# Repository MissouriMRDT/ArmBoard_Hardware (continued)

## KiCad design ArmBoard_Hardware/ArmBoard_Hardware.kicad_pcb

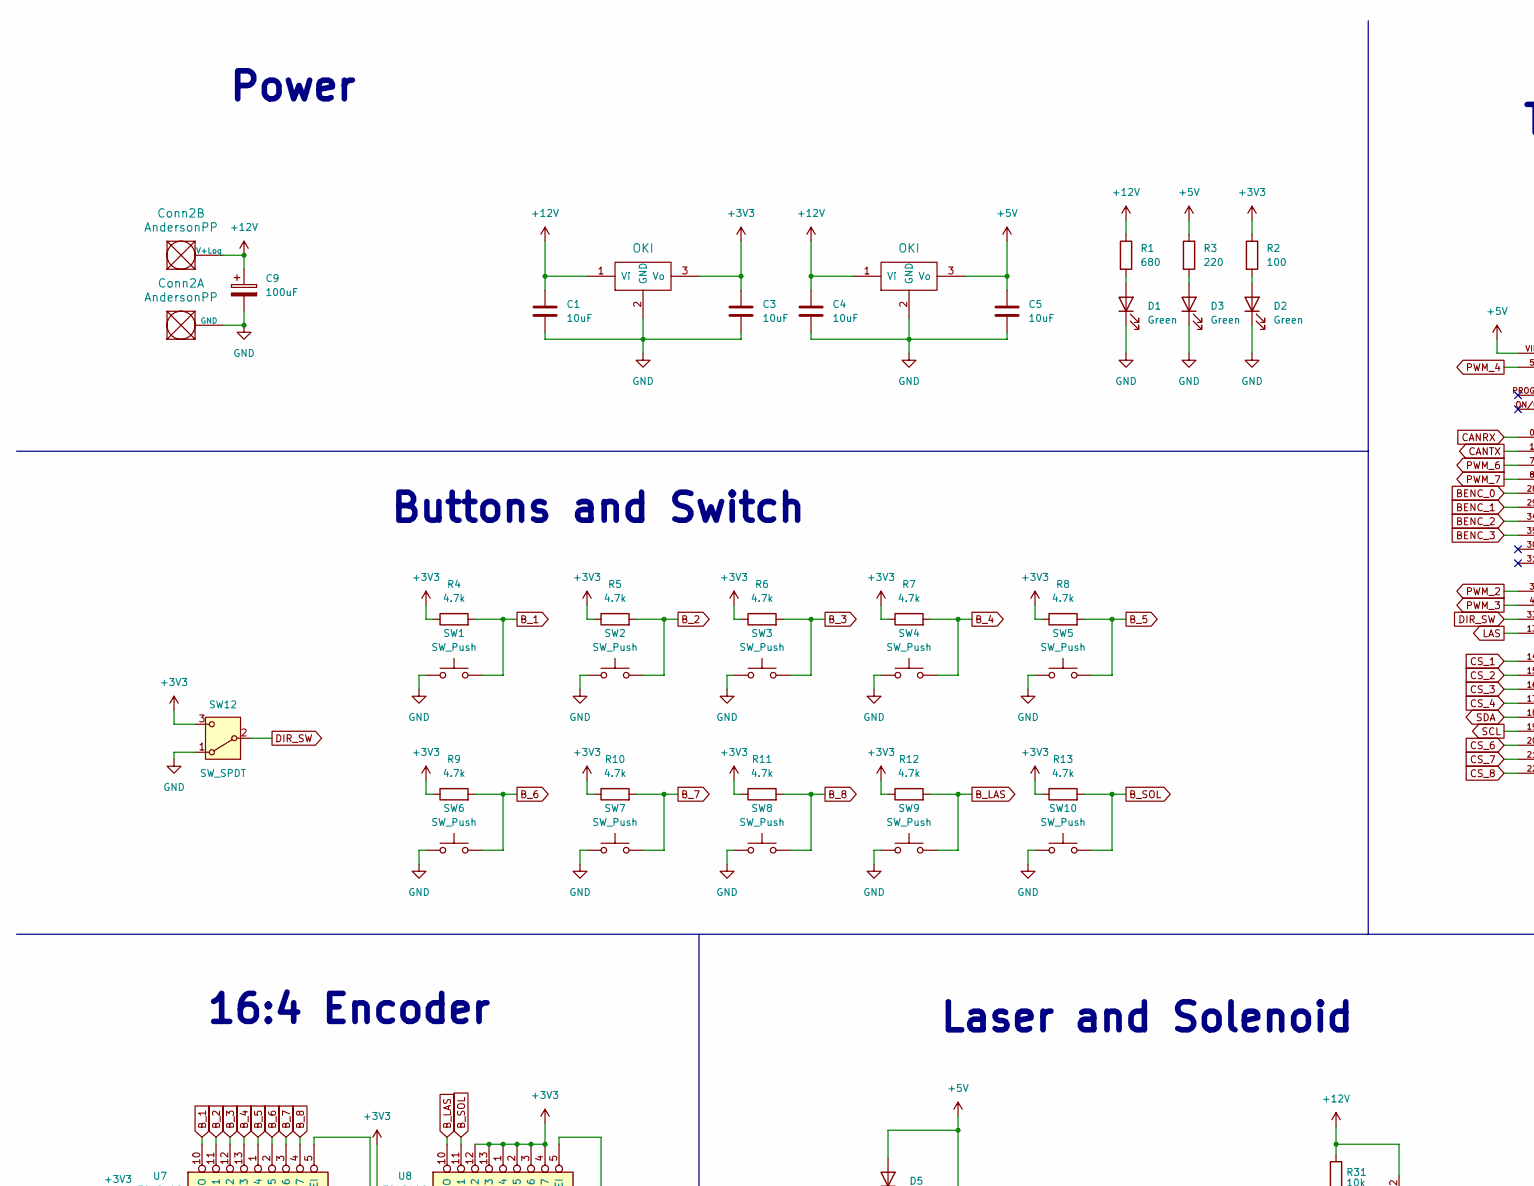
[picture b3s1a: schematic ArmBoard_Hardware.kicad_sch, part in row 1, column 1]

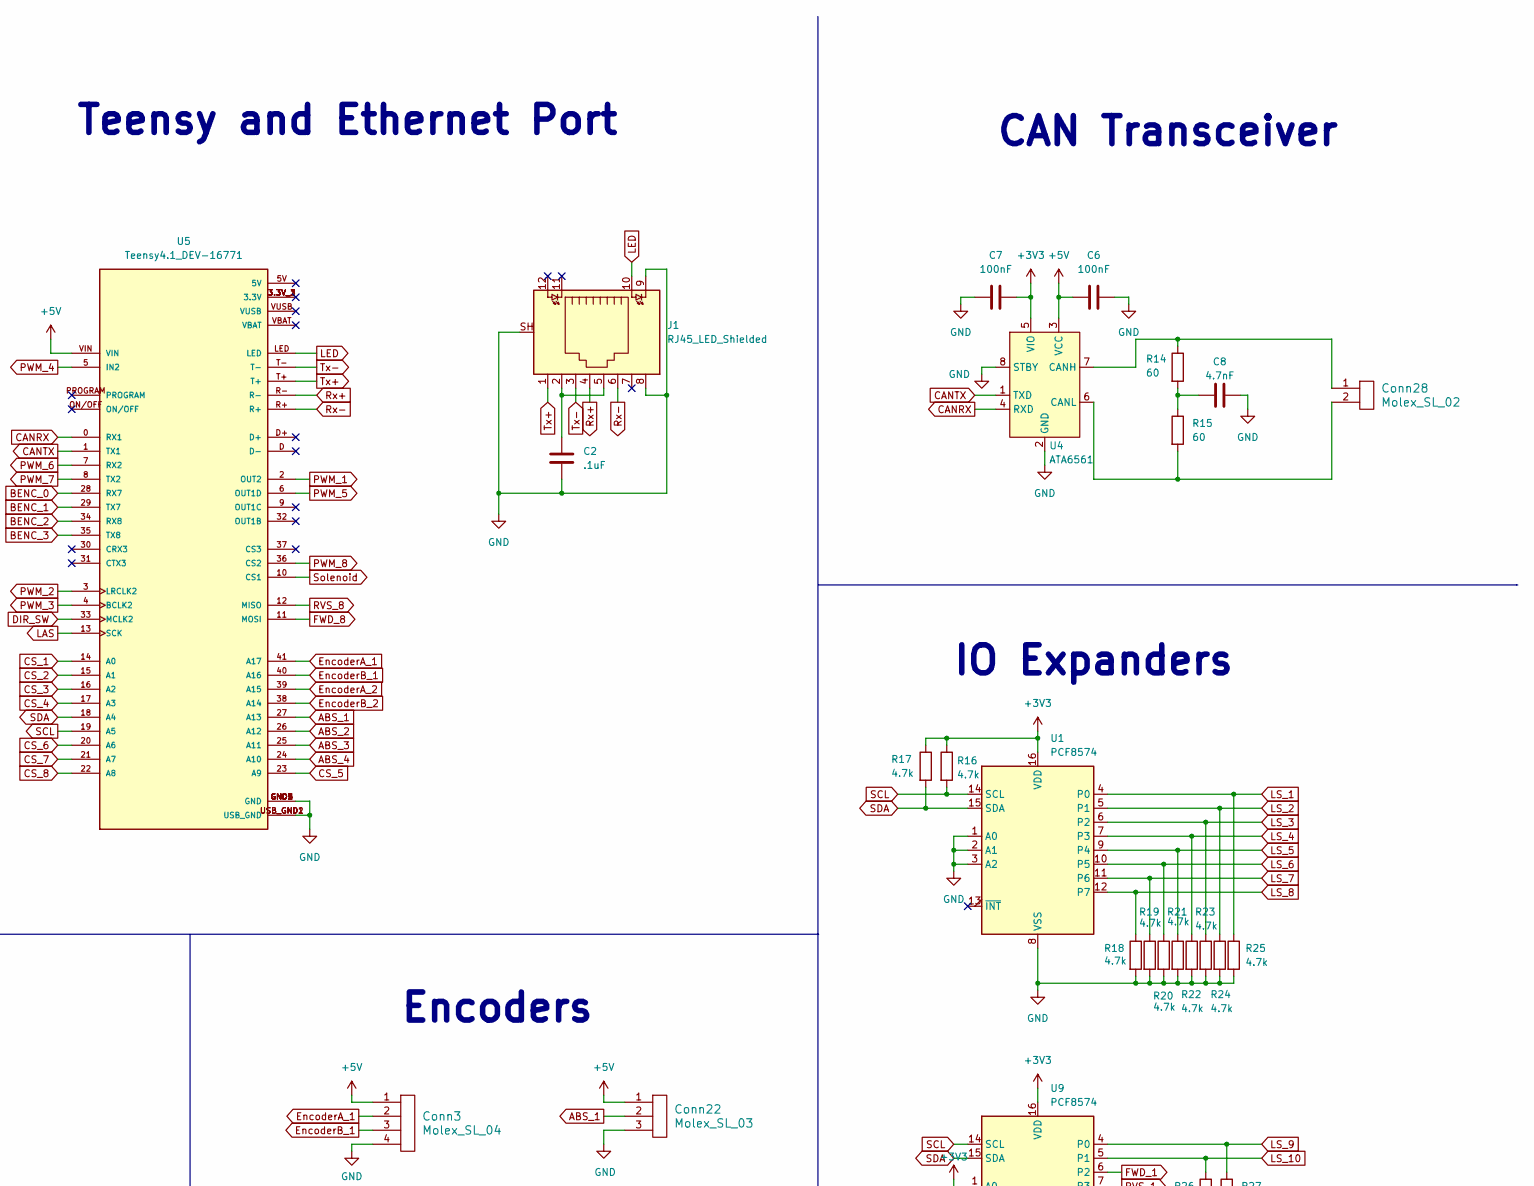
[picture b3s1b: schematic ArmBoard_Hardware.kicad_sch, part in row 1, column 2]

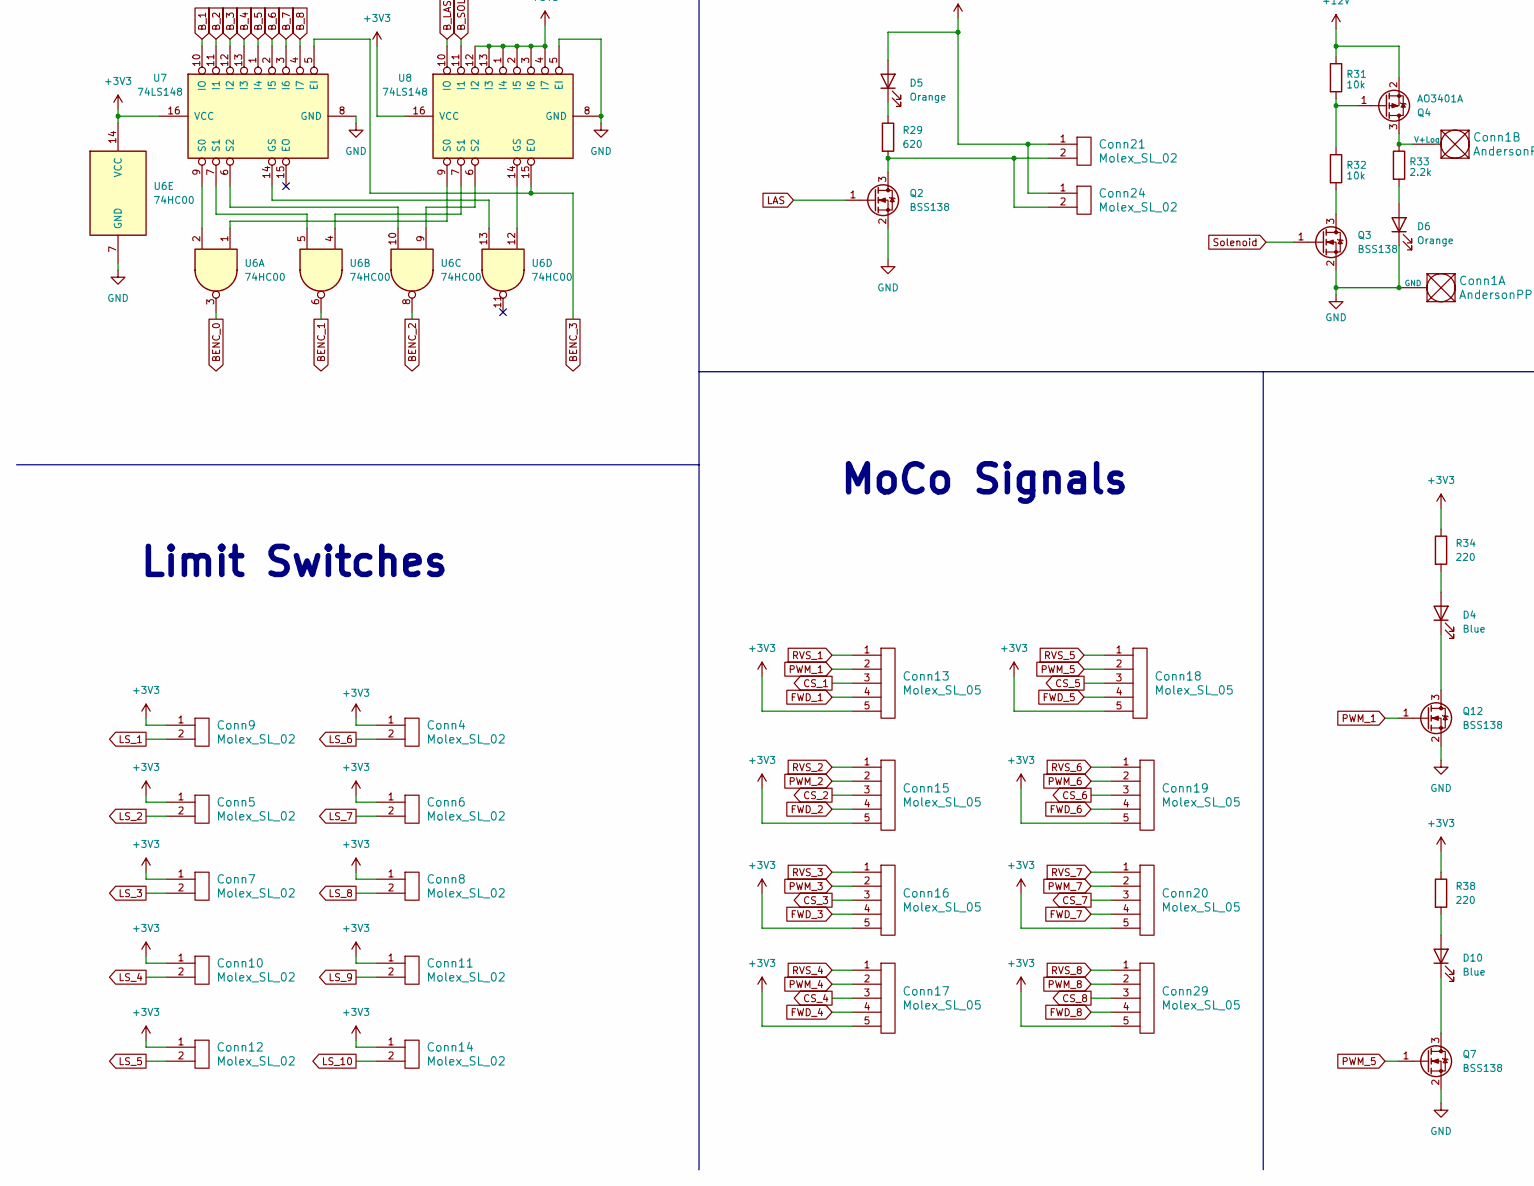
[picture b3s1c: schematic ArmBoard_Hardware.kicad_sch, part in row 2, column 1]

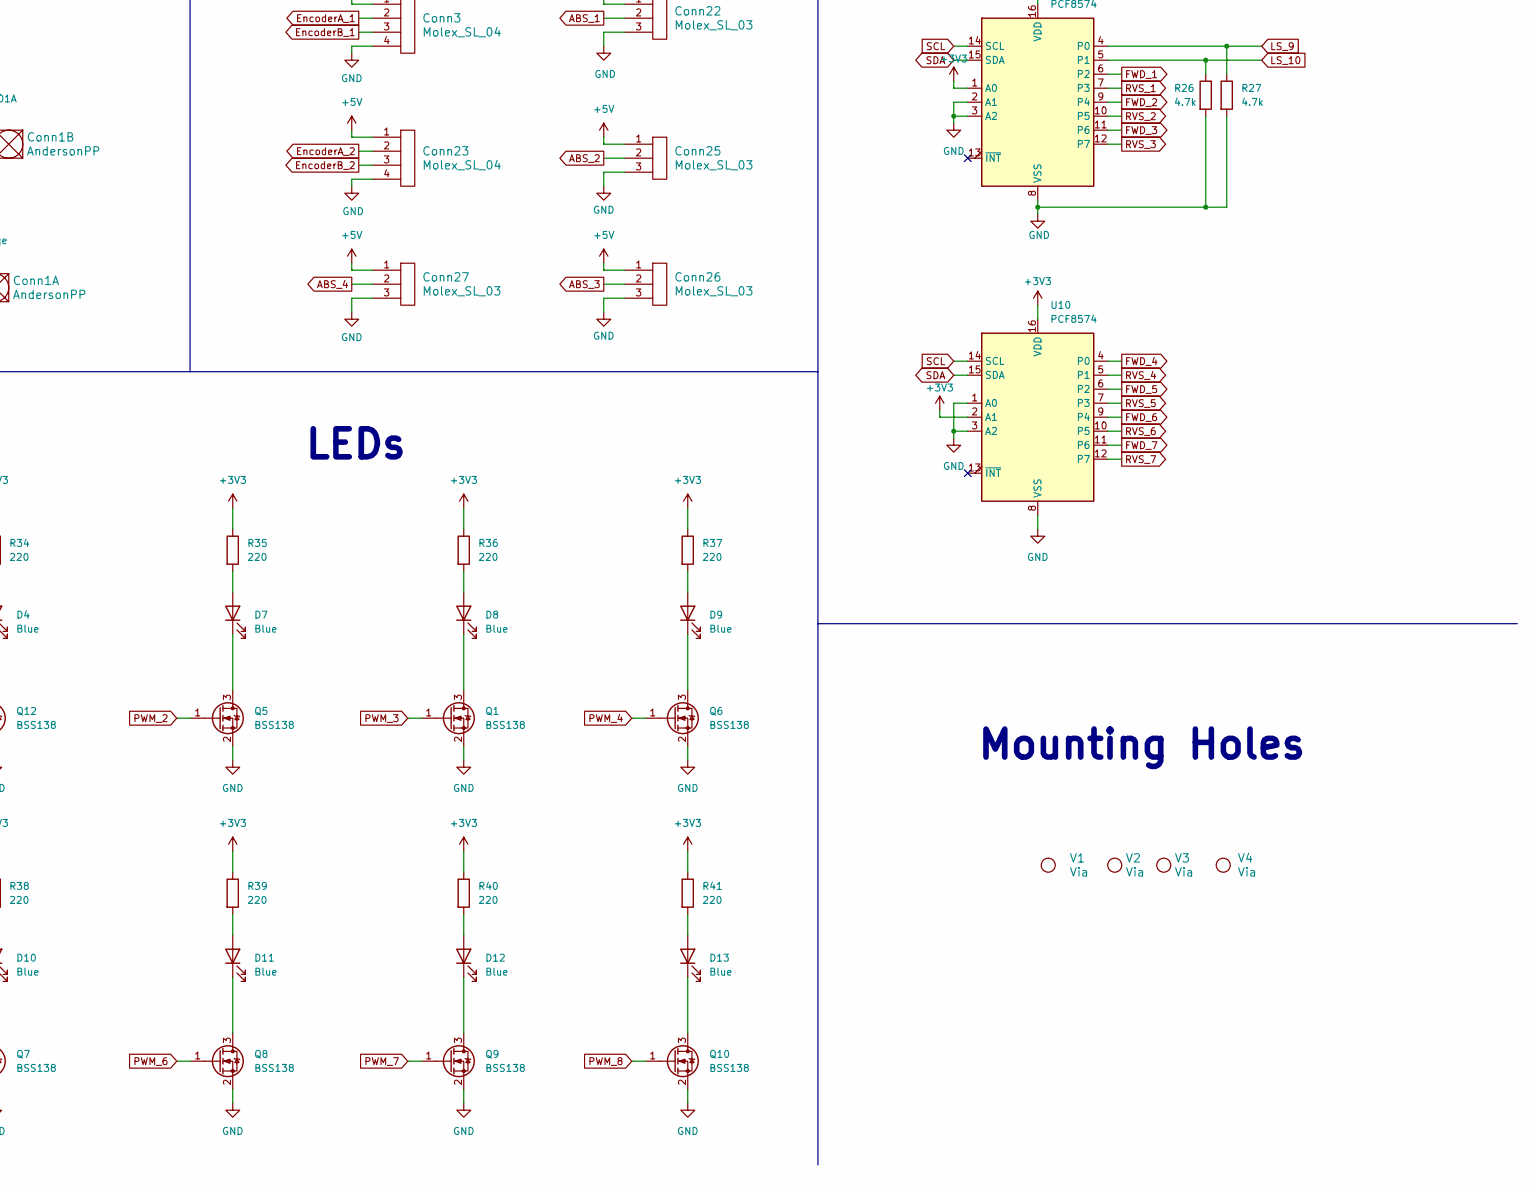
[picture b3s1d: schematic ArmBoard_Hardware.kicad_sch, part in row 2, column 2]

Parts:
C1, C3, C4, C5: 10uF; C_0603_1608Metric_Pad1.08x0.95mm_HandSolder
C2: .1uF; C_0603_1608Metric_Pad1.08x0.95mm_HandSolder
C6, C7: 100nF; C_0603_1608Metric_Pad1.08x0.95mm_HandSolder
C8: 4.7nF; C_0603_1608Metric_Pad1.08x0.95mm_HandSolder
C9: 100uF; CP_Radial_D6.3mm_P2.50mm
Conn1, Conn2: AndersonPP; Square_Anderson_2_H_Side_By_Side
Conn3, Conn23: Molex_SL_04; MOLEX_SL_04_Vertical
Conn4, Conn5, Conn6, Conn7, Conn8, Conn9, Conn10, Conn11, Conn12, Conn14, Conn21, Conn24, Conn28: Molex_SL_02; MOLEX_SL_02_Vertical
Conn13, Conn15, Conn16, Conn17, Conn18, Conn19, Conn20, Conn29: Molex_SL_05; MOLEX_SL_05_Vertical
Conn22, Conn25, Conn26, Conn27: Molex_SL_03; MOLEX_SL_03_Vertical
D1, D2, D3: Green; LED_0603_1608Metric_Pad1.05x0.95mm_HandSolder
D4, D7, D8, D9, D10, D11, D12, D13: Blue; LED_0603_1608Metric_Pad1.05x0.95mm_HandSolder
D5, D6: Orange; LED_0603_1608Metric_Pad1.05x0.95mm_HandSolder
J1: RJ45_LED_Shielded; RJ45_Teensy
Q1, Q2, Q3, Q5, Q6, Q7, Q8, Q9, Q10, Q12: BSS138; SOT-23
Q4: AO3401A; SOT-23
R1: 680; R_0603_1608Metric_Pad0.98x0.95mm_HandSolder
R2: 100; R_0603_1608Metric_Pad0.98x0.95mm_HandSolder
R3, R34, R35, R36, R37, R38, R39, R40, R41: 220; R_0603_1608Metric_Pad0.98x0.95mm_HandSolder
R4, R5, R6, R7, R8, R9, R10, R11, R12, R13, R16, R17, R18, R19, R20, R21, R22, R23, R24, R25, R26, R27: 4.7k; R_0603_1608Metric_Pad0.98x0.95mm_HandSolder
R14, R15: 60; R_0603_1608Metric_Pad0.98x0.95mm_HandSolder
R29: 620; R_0603_1608Metric_Pad0.98x0.95mm_HandSolder
R31, R32: 10k; R_0603_1608Metric_Pad0.98x0.95mm_HandSolder
R33: 2.2k; R_0603_1608Metric_Pad0.98x0.95mm_HandSolder
SW1, SW2, SW3, SW4, SW5, SW6, SW7, SW8, SW9, SW10: SW_Push; SW_SPST_TL3305A
SW12: SW_SPDT; SW_Slide_SPDT_Angled_CK_OS102011MA1Q
U1, U9, U10: PCF8574; SOIC-16W_7.5x10.3mm_P1.27mm
U2, U3: OKI; OKI_Horizontal
U4: ATA6561; SOIC-8_3.9x4.9mm_P1.27mm
U5: Teensy4.1_DEV-16771; Teensy_4_1_Ethernet; PARTREV 4.1
U6: 74HC00; SO-14_3.9x8.65mm_P1.27mm
U7, U8: 74LS148; SOIC-16_3.9x9.9mm_P1.27mm
V1, V2, V3, V4: Via; 4_40_Hole

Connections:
+3V3: C3.1, C7.1, Conn4.1, Conn5.1, Conn6.1, Conn7.1, Conn8.1, Conn9.1, Conn10.1, Conn11.1, Conn12.1, Conn13.5, Conn14.1, Conn15.5, Conn16.5, Conn17.5, Conn18.5, Conn19.5, Conn20.5, Conn29.5, R2.1, R4.1, R5.1, R6.1, R7.1, R8.1, R9.1, R10.1, R11.1, R12.1, R13.1, R16.1, R17.1, R34.1, R35.1, R36.1, R37.1, R38.1, R39.1, R40.1, R41.1, SW12.3 (C), U1.16 (VDD), U3.3 (Vo), U4.5 (VIO), U6.14 (VCC), U7.16 (VCC), U8.1 (I4), U8.2 (I5), U8.3 (I6), U8.4 (I7), U8.12 (I2), U8.13 (I3), U8.16 (VCC), U9.1 (A0), U9.16 (VDD), U10.2 (A1), U10.16 (VDD)
+5V: C5.1, C6.1, Conn3.1, Conn21.1, Conn22.1, Conn23.1, Conn24.1, Conn25.1, Conn26.1, Conn27.1, D5.2 (A), R3.1, U2.3 (Vo), U4.3 (VCC), U5.VIN
+12V: C1.1, C4.1, C9.1, Conn2.2 (V+Log), Q4.2 (S), R1.1, R31.1, U2.1 (Vi), U3.1 (Vi)
ABS_1: Conn22.2, U5.27 (A13)
ABS_2: Conn25.2, U5.26 (A12)
ABS_3: Conn26.2, U5.25 (A11)
ABS_4: Conn27.2, U5.24 (A10)
BENC_0: U5.28 (RX7), U6.3
BENC_1: U5.29 (TX7), U6.6
BENC_2: U5.34 (RX8), U6.8
BENC_3: U5.35 (TX8), U7.5 (EI), U8.15 (EO)
B_1: R4.2, SW1.2, U7.10 (IO)
B_2: R5.2, SW2.2, U7.11 (I1)
B_3: R6.2, SW3.2, U7.12 (I2)
B_4: R7.2, SW4.2, U7.13 (I3)
B_5: R8.2, SW5.2, U7.1 (I4)
B_6: R9.2, SW6.2, U7.2 (I5)
B_7: R10.2, SW7.2, U7.3 (I6)
B_8: R11.2, SW8.2, U7.4 (I7)
B_LAS: R12.2, SW9.2, U8.10 (IO)
B_SOL: R13.2, SW10.2, U8.11 (I1)
CANRX: U4.4 (RXD), U5.0 (RX1)
CANTX: U4.1 (TXD), U5.1 (TX1)
CS_1: Conn13.3, U5.14 (A0)
CS_2: Conn15.3, U5.15 (A1)
CS_3: Conn16.3, U5.16 (A2)
CS_4: Conn17.3, U5.17 (A3)
CS_5: Conn18.3, U5.23 (A9)
CS_6: Conn19.3, U5.20 (A6)
CS_7: Conn20.3, U5.21 (A7)
CS_8: Conn29.3, U5.22 (A8)
DIR_SW: SW12.2 (B), U5.33 (MCLK2)
EncoderA_1: Conn3.2, U5.41 (A17)
EncoderA_2: Conn23.2, U5.39 (A15)
EncoderB_1: Conn3.3, U5.40 (A16)
EncoderB_2: Conn23.3, U5.38 (A14)
FWD_1: Conn13.4, U9.6 (P2)
FWD_2: Conn15.4, U9.9 (P4)
FWD_3: Conn16.4, U9.11 (P6)
FWD_4: Conn17.4, U10.4 (P0)
FWD_5: Conn18.4, U10.6 (P2)
FWD_6: Conn19.4, U10.9 (P4)
FWD_7: Conn20.4, U10.11 (P6)
FWD_8: Conn29.4, U5.11 (MOSI)
GND: C1.2, C2.2, C3.2, C4.2, C5.2, C6.2, C7.2, C8.2, C9.2, Conn1.1 (GND), Conn2.1 (GND), Conn3.4, Conn22.3, Conn23.4, Conn25.3, Conn26.3, Conn27.3, D1.1 (K), D2.1 (K), D3.1 (K), D6.1 (K), J1.8, J1.9, J1.SH, Q1.2 (S), Q2.2 (S), Q3.2 (S), Q5.2 (S), Q6.2 (S), Q7.2 (S), Q8.2 (S), Q9.2 (S), Q10.2 (S), Q12.2 (S), R18.2, R19.2, R20.2, R21.2, R22.2, R23.2, R24.2, R25.2, R26.2, R27.2, SW1.1, SW2.1, SW3.1, SW4.1, SW5.1, SW6.1, SW7.1, SW8.1, SW9.1, SW10.1, SW12.1 (A), U1.1 (A0), U1.2 (A1), U1.3 (A2), U1.8 (VSS), U2.2 (GND), U3.2 (GND), U4.2 (GND), U4.8 (STBY), U5.GND1 (GND), U5.GND2 (GND), U5.GND3 (GND), U5.GND4 (GND), U5.GND5 (GND), U5.USB_GND1 (USB_GND), U5.USB_GND2 (USB_GND), U6.7 (GND), U7.8 (GND), U8.5 (EI), U8.8 (GND), U9.2 (A1), U9.3 (A2), U9.8 (VSS), U10.1 (A0), U10.3 (A2), U10.8 (VSS)
LAS: Q2.1 (G), U5.13 (SCK)
LED: J1.10, U5.LED
LS_1: Conn9.2, R25.1, U1.4 (P0)
LS_2: Conn5.2, R24.1, U1.5 (P1)
LS_3: Conn7.2, R23.1, U1.6 (P2)
LS_4: Conn10.2, R22.1, U1.7 (P3)
LS_5: Conn12.2, R21.1, U1.9 (P4)
LS_6: Conn4.2, R20.1, U1.10 (P5)
LS_7: Conn6.2, R19.1, U1.11 (P6)
LS_8: Conn8.2, R18.1, U1.12 (P7)
LS_9: Conn11.2, R27.1, U9.4 (P0)
LS_10: Conn14.2, R26.1, U9.5 (P1)
unnamed: C2.1, J1.2, J1.5
unnamed: C8.1, R14.2, R15.1
unnamed: Conn1.2 (V+Log), Q4.3 (D), R33.1
unnamed: D1.2 (A), R1.2
unnamed: D2.2 (A), R2.2
unnamed: D3.2 (A), R3.2
unnamed: D4.2 (A), R34.2
unnamed: D4.1 (K), Q12.3 (D)
unnamed: D5.1 (K), R29.1
unnamed: D6.2 (A), R33.2
unnamed: D7.2 (A), R35.2
unnamed: D7.1 (K), Q5.3 (D)
unnamed: D8.2 (A), R36.2
unnamed: D8.1 (K), Q1.3 (D)
unnamed: D9.2 (A), R37.2
unnamed: D9.1 (K), Q6.3 (D)
unnamed: D10.2 (A), R38.2
unnamed: D10.1 (K), Q7.3 (D)
unnamed: D11.2 (A), R39.2
unnamed: D11.1 (K), Q8.3 (D)
unnamed: D12.2 (A), R40.2
unnamed: D12.1 (K), Q9.3 (D)
unnamed: D13.2 (A), R41.2
unnamed: D13.1 (K), Q10.3 (D)
unnamed: Conn21.2, Conn24.2, Q2.3 (D), R29.2
unnamed: Q3.3 (D), R32.2
unnamed: Q4.1 (G), R31.2, R32.1
unnamed: Conn28.1, R14.1, U4.7 (CANH)
unnamed: Conn28.2, R15.2, U4.6 (CANL)
unnamed: U6.13, U7.14 (GS)
unnamed: U6.2, U7.9 (S0)
unnamed: U6.5, U7.7 (S1)
unnamed: U6.10, U7.6 (S2)
unnamed: U6.12, U8.14 (GS)
unnamed: U6.1, U8.9 (S0)
unnamed: U6.4, U8.7 (S1)
unnamed: U6.9, U8.6 (S2)
PWM_1: Conn13.2, Q12.1 (G), U5.2 (OUT2)
PWM_2: Conn15.2, Q5.1 (G), U5.3 (LRCLK2)
PWM_3: Conn16.2, Q1.1 (G), U5.4 (BCLK2)
PWM_4: Conn17.2, Q6.1 (G), U5.5 (IN2)
PWM_5: Conn18.2, Q7.1 (G), U5.6 (OUT1D)
PWM_6: Conn19.2, Q8.1 (G), U5.7 (RX2)
PWM_7: Conn20.2, Q9.1 (G), U5.8 (TX2)
PWM_8: Conn29.2, Q10.1 (G), U5.36 (CS2)
RVS_1: Conn13.1, U9.7 (P3)
RVS_2: Conn15.1, U9.10 (P5)
RVS_3: Conn16.1, U9.12 (P7)
RVS_4: Conn17.1, U10.5 (P1)
RVS_5: Conn18.1, U10.7 (P3)
RVS_6: Conn19.1, U10.10 (P5)
RVS_7: Conn20.1, U10.12 (P7)
RVS_8: Conn29.1, U5.12 (MISO)
Rx+: J1.4, U5.R-
Rx-: J1.6, U5.R+
SCL: R16.2, U1.14 (SCL), U5.19 (A5), U9.14 (SCL), U10.14 (SCL)
SDA: R17.2, U1.15 (SDA), U5.18 (A4), U9.15 (SDA), U10.15 (SDA)
Solenoid: Q3.1 (G), U5.10 (CS1)
Tx+: J1.1, U5.T+
Tx-: J1.3, U5.T-

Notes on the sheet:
Buttons and Switch
LEDs
Teensy and Ethernet Port
Limit Switches
Encoders
Power
MoCo Signals
16:4 Encoder
IO Expanders
Laser and Solenoid
Mounting Holes
CAN Transceiver

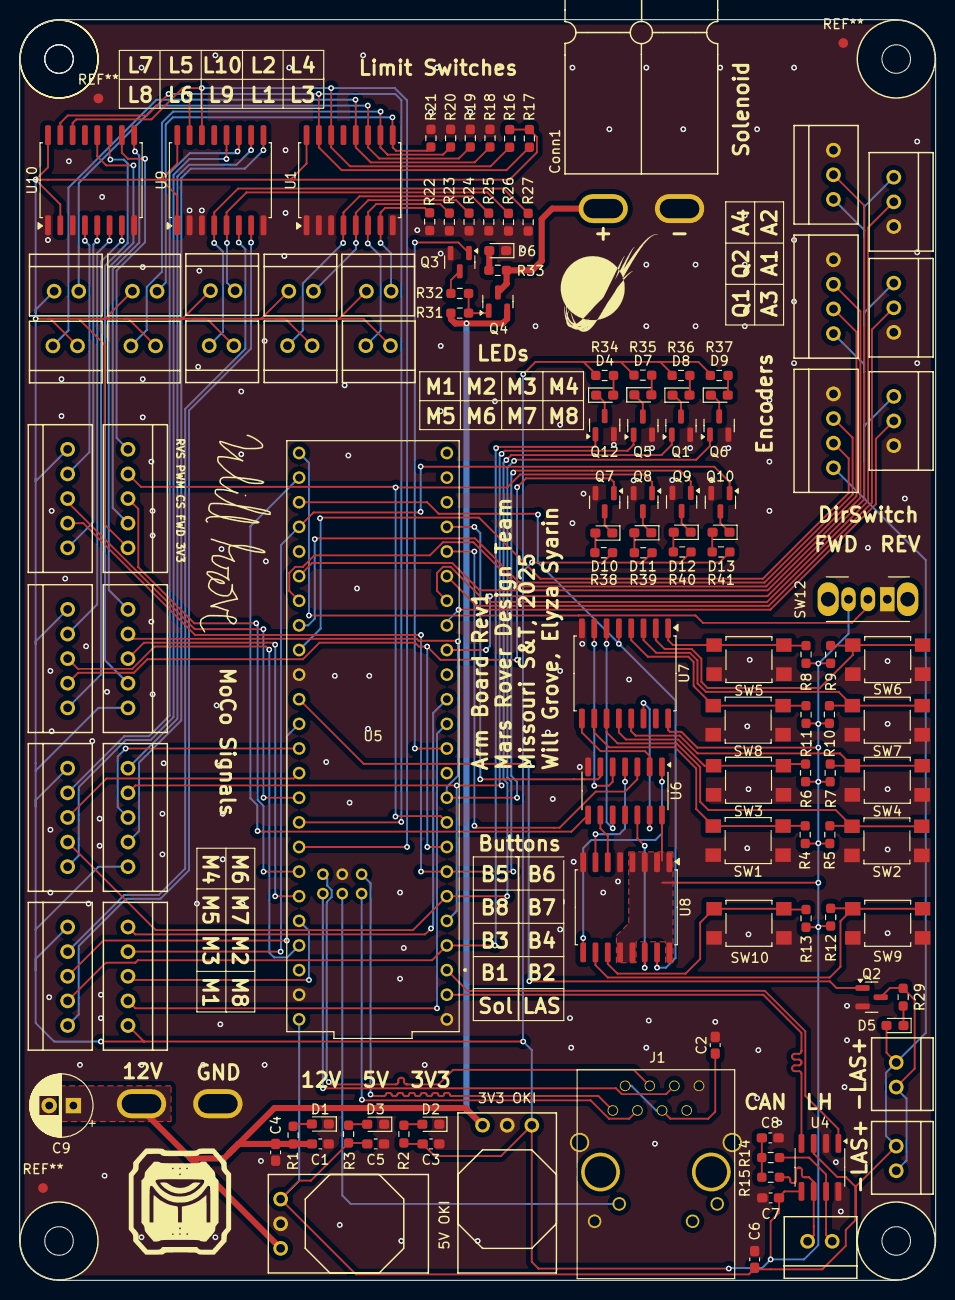
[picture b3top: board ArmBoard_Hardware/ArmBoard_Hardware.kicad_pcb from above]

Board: 2 copper layers, 94.5 x 130.0 mm, 128 parts (1 on the bottom side), 117 nets.

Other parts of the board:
V2#2, V3#2: Via; 4_40_Hole

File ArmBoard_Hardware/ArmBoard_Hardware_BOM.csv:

"Id";"Designator";"Footprint";"Quantity";"Designation";"Supplier and ref";
1;"C7,C6";"C_0603_1608Metric_Pad1.08x0.95mm_HandSolder";2;"100nF";;;
2;"U4";"SOIC-8_3.9x4.9mm_P1.27mm";1;"ATA6561";;;
3;"R36,R41,R35,R37,R40,R38,R3,R34,R39";"R_0603_1608Metric_Pad0.98x0.95mm_HandSolder";9;"220";;;
4;"SW5,SW4,SW1,SW9,SW10,SW3,SW8,SW6,SW2,SW7";"SW_SPST_TL3305A";10;"SW_Push";;;
5;"C9";"CP_Radial_D6.3mm_P2.50mm";1;"100uF";;;
6;"U3";"OKI_Horizontal";1;"3V3 OKI";;;
7;"R10,R22,R20,R19,R16,R13,R24,R7,R21,R17,R5,R25,R18,R11,R8,R9,R26,R12,R6,R23,R27,R4";"R_0603_1608Metric_Pad0.98x0.95mm_HandSolder";22;"4.7k";;;
8;"Q12,Q9,Q2,Q6,Q7,Q3,Q5,Q8,Q10,Q1";"SOT-23";10;"BSS138";;;
9;"Conn20,Conn15,Conn13,Conn16,Conn17,Conn29,Conn19,Conn18";"MOLEX_SL_05_Vertical";8;"Molex_SL_05";;;
10;"Conn1,Conn2";"Square_Anderson_2_H_Side_By_Side";2;"AndersonPP";;;
11;"Conn28,Conn7,Conn21,Conn24,Conn8,Conn4,Conn9,Conn5,Conn10,Conn14,Conn12,Conn11,Conn6";"MOLEX_SL_02_Vertical";13;"Molex_SL_02";;;
12;"U5";"Teensy_4_1_Ethernet";1;"Teensy4.1_DEV-16771";;;
13;"V4,V3,V2,V2,V3";"4_40_Hole";5;"Via";;;
14;"C5,C3,C1,C4";"C_0603_1608Metric_Pad1.08x0.95mm_HandSolder";4;"10uF";;;
15;"Q4";"SOT-23";1;"AO3401A";;;
16;"D7,D12,D8,D9,D10,D11,D13,D4";"LED_0603_1608Metric_Pad1.05x0.95mm_HandSolder";8;"Blue";;;
17;"D5,D6";"LED_0603_1608Metric_Pad1.05x0.95mm_HandSolder";2;"Orange";;;
18;"R31,R32";"R_0603_1608Metric_Pad0.98x0.95mm_HandSolder";2;"10k";;;
19;"D3,D1,D2";"LED_0603_1608Metric_Pad1.05x0.95mm_HandSolder";3;"Green";;;
20;"U1,U10,U9";"SOIC-16W_7.5x10.3mm_P1.27mm";3;"PCF8574";;;
21;"R2";"R_0603_1608Metric_Pad0.98x0.95mm_HandSolder";1;"100";;;
22;"Conn26,Conn27,Conn25,Conn22";"MOLEX_SL_03_Vertical";4;"Molex_SL_03";;;
23;"R1";"R_0603_1608Metric_Pad0.98x0.95mm_HandSolder";1;"680";;;
24;"C8";"C_0603_1608Metric_Pad1.08x0.95mm_HandSolder";1;"4.7nF";;;
25;"R15,R14";"R_0603_1608Metric_Pad0.98x0.95mm_HandSolder";2;"60";;;
26;"SW12";"SW_Slide_SPDT_Angled_CK_OS102011MA1Q";1;"SW_SPDT";;;
27;"R29";"R_0603_1608Metric_Pad0.98x0.95mm_HandSolder";1;"620";;;
28;"U2";"OKI_Horizontal";1;"5V OKI";;;
29;"C2";"C_0603_1608Metric_Pad1.08x0.95mm_HandSolder";1;".1uF";;;
30;"Conn23,Conn3";"MOLEX_SL_04_Vertical";2;"Molex_SL_04";;;
31;"G***";"0_MRDT_Logo_10mm";1;"LOGO";;;
32;"J1";"RJ45_Teensy";1;"RJ45_LED_Shielded";;;
33;"R33";"R_0603_1608Metric_Pad0.98x0.95mm_HandSolder";1;"2.2k";;;
34;"U6";"SO-14_3.9x8.65mm_P1.27mm";1;"74HC00";;;
35;"U8,U7";"SOIC-16W_7.5x10.3mm_P1.27mm";2;"74LS148";;;

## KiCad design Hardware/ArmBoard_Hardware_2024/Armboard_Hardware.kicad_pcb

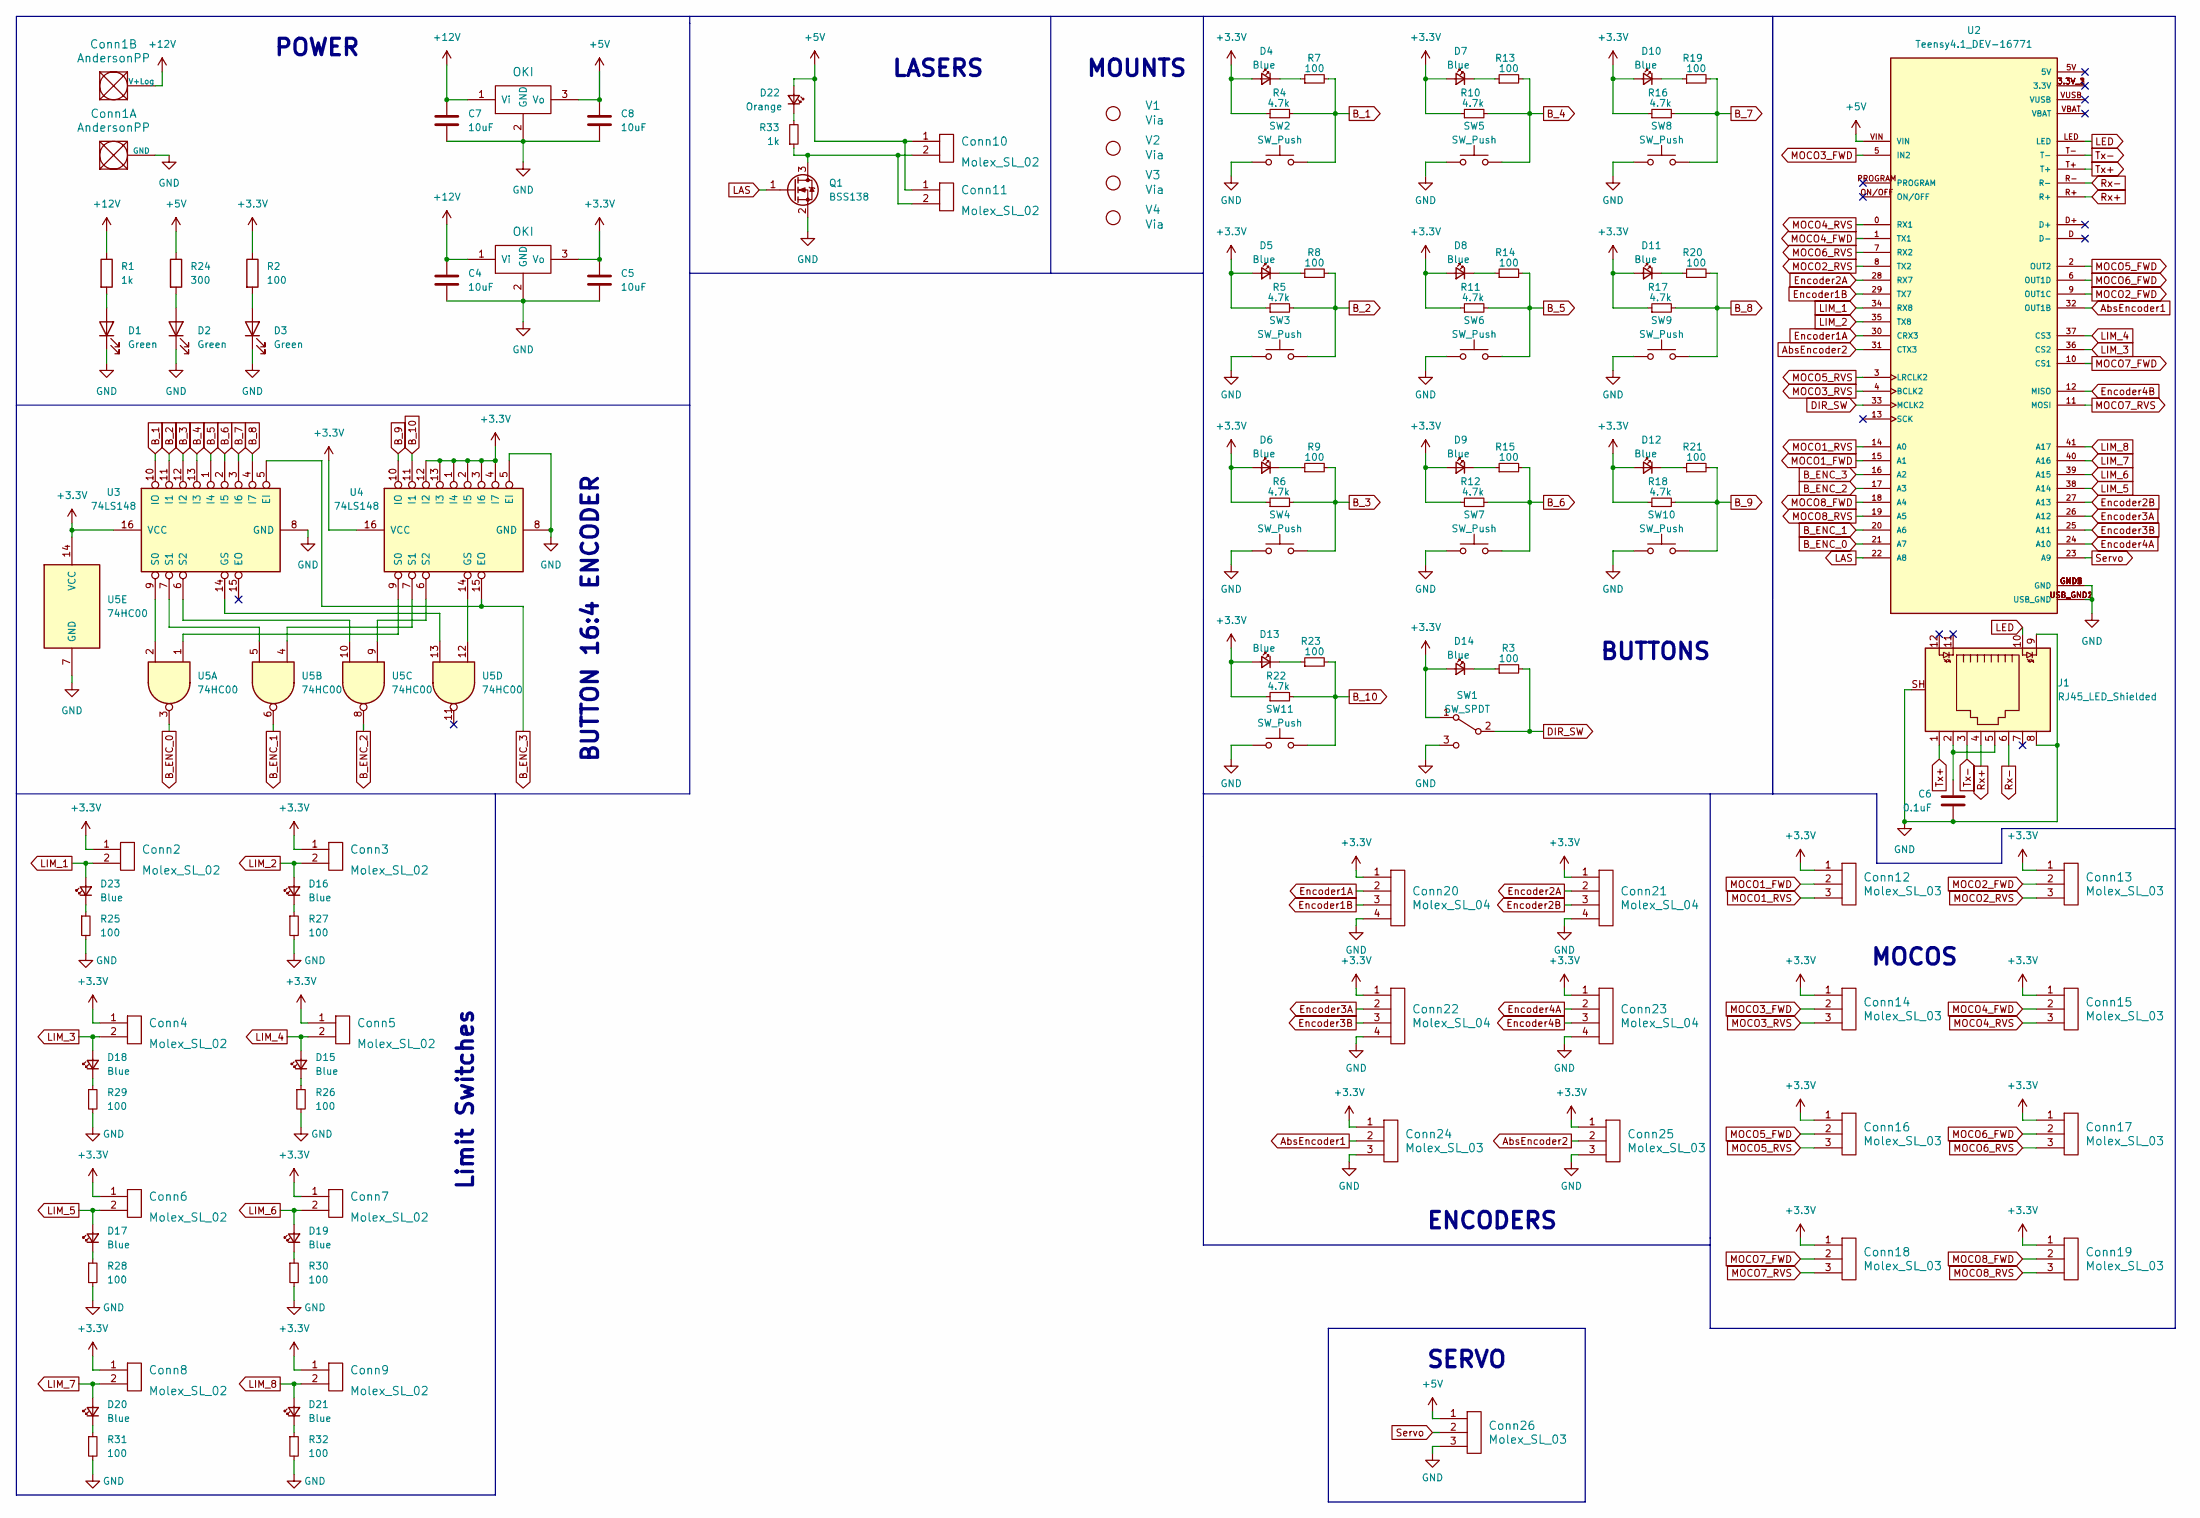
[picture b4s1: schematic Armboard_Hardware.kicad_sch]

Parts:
C4, C5, C7, C8: 10uF; C_0603_1608Metric_Pad1.08x0.95mm_HandSolder
C6: 0.1uF; C_0603_1608Metric_Pad1.08x0.95mm_HandSolder
Conn1: AndersonPP; Square_Anderson_2_H_Side_By_Side
Conn2, Conn3, Conn4, Conn5, Conn6, Conn7, Conn8, Conn9, Conn10, Conn11: Molex_SL_02; MOLEX_SL_02_Horizontal
Conn12, Conn13, Conn14, Conn15, Conn16, Conn17, Conn18, Conn19: Molex_SL_03; MOLEX_SL_03_Vertical
Conn20, Conn21, Conn22, Conn23: Molex_SL_04; MOLEX_SL_04_Horizontal
Conn24, Conn25, Conn26: Molex_SL_03; MOLEX_SL_03_Horizontal
D1, D2, D3: Green; LED_0603_1608Metric_Pad1.05x0.95mm_HandSolder
D4, D5, D6, D7, D8, D9, D10, D11, D12, D13, D14, D15, D16, D17, D18, D19, D20, D21, D23: Blue; LED_0603_1608Metric_Pad1.05x0.95mm_HandSolder
D22: Orange; LED_0603_1608Metric_Pad1.05x0.95mm_HandSolder
J1: RJ45_LED_Shielded; RJ45_Teensy
Q1: BSS138; SOT-23
R1, R33: 1k; R_0603_1608Metric_Pad0.98x0.95mm_HandSolder
R2, R3, R7, R8, R9, R13, R14, R15, R19, R20, R21, R23, R25, R26, R27, R28, R29, R30, R31, R32: 100; R_0603_1608Metric_Pad0.98x0.95mm_HandSolder
R4, R5, R6, R10, R11, R12, R16, R17, R18, R22: 4.7k; R_0603_1608Metric_Pad0.98x0.95mm_HandSolder
R24: 300; R_0603_1608Metric_Pad0.98x0.95mm_HandSolder
SW1: SW_SPDT; SW_Slide_1P2T_CK_OS102011MS2Q
SW2, SW3, SW4, SW5, SW6, SW7, SW8, SW9, SW10, SW11: SW_Push; SW_SPST_TL3305A
U1, U6: OKI; OKI_Horizontal
U2: Teensy4.1_DEV-16771; Teensy_4_1_Ethernet; PARTREV 4.1
U3, U4: 74LS148; SOIC-16_3.9x9.9mm_P1.27mm
U5: 74HC00; SO-14_3.9x8.65mm_P1.27mm
V1, V2, V3, V4: Via; 4_40_Hole_Corner

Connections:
+3.3V: C5.1, Conn2.1, Conn3.1, Conn4.1, Conn5.1, Conn6.1, Conn7.1, Conn8.1, Conn9.1, Conn12.1, Conn13.1, Conn14.1, Conn15.1, Conn16.1, Conn17.1, Conn18.1, Conn19.1, Conn20.1, Conn21.1, Conn22.1, Conn23.1, Conn24.1, Conn25.1, D4.2 (A), D5.2 (A), D6.2 (A), D7.2 (A), D8.2 (A), D9.2 (A), D10.2 (A), D11.2 (A), D12.2 (A), D13.2 (A), D14.2 (A), R2.1, R4.1, R5.1, R6.1, R10.1, R11.1, R12.1, R16.1, R17.1, R18.1, R22.1, SW1.1 (A), U1.3 (Vo), U3.16 (VCC), U4.1 (I4), U4.2 (I5), U4.3 (I6), U4.4 (I7), U4.12 (I2), U4.13 (I3), U4.16 (VCC), U5.14 (VCC)
+5V: C8.1, Conn10.1, Conn11.1, Conn26.1, D22.2 (A), R24.1, U2.VIN, U6.3 (Vo)
+12V: C4.1, C7.1, Conn1.2 (V+Log), R1.1, U1.1 (Vi), U6.1 (Vi)
AbsEncoder1: Conn24.2, U2.32 (OUT1B)
AbsEncoder2: Conn25.2, U2.31 (CTX3)
B_1: R4.2, R7.2, SW2.2, U3.10 (IO)
B_2: R5.2, R8.2, SW3.2, U3.11 (I1)
B_3: R6.2, R9.2, SW4.2, U3.12 (I2)
B_4: R10.2, R13.2, SW5.2, U3.13 (I3)
B_5: R11.2, R14.2, SW6.2, U3.1 (I4)
B_6: R12.2, R15.2, SW7.2, U3.2 (I5)
B_7: R16.2, R19.2, SW8.2, U3.3 (I6)
B_8: R17.2, R20.2, SW9.2, U3.4 (I7)
B_9: R18.2, R21.2, SW10.2, U4.10 (IO)
B_10: R22.2, R23.2, SW11.2, U4.11 (I1)
B_ENC_0: U2.21 (A7), U5.3
B_ENC_1: U2.20 (A6), U5.6
B_ENC_2: U2.17 (A3), U5.8
B_ENC_3: U2.16 (A2), U3.5 (EI), U4.15 (EO)
DIR_SW: R3.2, SW1.2 (B), U2.33 (MCLK2)
Encoder1A: Conn20.2, U2.30 (CRX3)
Encoder1B: Conn20.3, U2.29 (TX7)
Encoder2A: Conn21.2, U2.28 (RX7)
Encoder2B: Conn21.3, U2.27 (A13)
Encoder3A: Conn22.2, U2.26 (A12)
Encoder3B: Conn22.3, U2.25 (A11)
Encoder4A: Conn23.2, U2.24 (A10)
Encoder4B: Conn23.3, U2.12 (MISO)
GND: C4.2, C5.2, C6.1, C7.2, C8.2, Conn1.1 (GND), Conn20.4, Conn21.4, Conn22.4, Conn23.4, Conn24.3, Conn25.3, Conn26.3, D1.1 (K), D2.1 (K), D3.1 (K), J1.8, J1.9, J1.SH, Q1.2 (S), R25.2, R26.2, R27.2, R28.2, R29.2, R30.2, R31.2, R32.2, SW1.3 (C), SW2.1, SW3.1, SW4.1, SW5.1, SW6.1, SW7.1, SW8.1, SW9.1, SW10.1, SW11.1, U1.2 (GND), U2.GND1 (GND), U2.GND2 (GND), U2.GND3 (GND), U2.GND4 (GND), U2.GND5 (GND), U2.USB_GND1 (USB_GND), U2.USB_GND2 (USB_GND), U3.8 (GND), U4.5 (EI), U4.8 (GND), U5.7 (GND), U6.2 (GND)
LAS: Q1.1 (G), U2.22 (A8)
LED: J1.10, U2.LED
LIM_1: Conn2.2, D23.2 (A), U2.34 (RX8)
LIM_2: Conn3.2, D16.2 (A), U2.35 (TX8)
LIM_3: Conn4.2, D18.2 (A), U2.36 (CS2)
LIM_4: Conn5.2, D15.2 (A), U2.37 (CS3)
LIM_5: Conn6.2, D17.2 (A), U2.38 (A14)
LIM_6: Conn7.2, D19.2 (A), U2.39 (A15)
LIM_7: Conn8.2, D20.2 (A), U2.40 (A16)
LIM_8: Conn9.2, D21.2 (A), U2.41 (A17)
MOCO1_FWD: Conn12.2, U2.15 (A1)
MOCO1_RVS: Conn12.3, U2.14 (A0)
MOCO2_FWD: Conn13.2, U2.9 (OUT1C)
MOCO2_RVS: Conn13.3, U2.8 (TX2)
MOCO3_FWD: Conn14.2, U2.5 (IN2)
MOCO3_RVS: Conn14.3, U2.4 (BCLK2)
MOCO4_FWD: Conn15.2, U2.1 (TX1)
MOCO4_RVS: Conn15.3, U2.0 (RX1)
MOCO5_FWD: Conn16.2, U2.2 (OUT2)
MOCO5_RVS: Conn16.3, U2.3 (LRCLK2)
MOCO6_FWD: Conn17.2, U2.6 (OUT1D)
MOCO6_RVS: Conn17.3, U2.7 (RX2)
MOCO7_FWD: Conn18.2, U2.10 (CS1)
MOCO7_RVS: Conn18.3, U2.11 (MOSI)
MOCO8_FWD: Conn19.2, U2.18 (A4)
MOCO8_RVS: Conn19.3, U2.19 (A5)
unnamed: C6.2, J1.2, J1.5
unnamed: D1.2 (A), R1.2
unnamed: D2.2 (A), R24.2
unnamed: D3.2 (A), R2.2
unnamed: D4.1 (K), R7.1
unnamed: D5.1 (K), R8.1
unnamed: D6.1 (K), R9.1
unnamed: D7.1 (K), R13.1
unnamed: D8.1 (K), R14.1
unnamed: D9.1 (K), R15.1
unnamed: D10.1 (K), R19.1
unnamed: D11.1 (K), R20.1
unnamed: D12.1 (K), R21.1
unnamed: D13.1 (K), R23.1
unnamed: D14.1 (K), R3.1
unnamed: D15.1 (K), R26.1
unnamed: D16.1 (K), R27.1
unnamed: D17.1 (K), R28.1
unnamed: D18.1 (K), R29.1
unnamed: D19.1 (K), R30.1
unnamed: D20.1 (K), R31.1
unnamed: D21.1 (K), R32.1
unnamed: D22.1 (K), R33.2
unnamed: D23.1 (K), R25.1
unnamed: Conn10.2, Conn11.2, Q1.3 (D), R33.1
unnamed: U3.14 (GS), U5.13
unnamed: U3.9 (S0), U5.2
unnamed: U3.7 (S1), U5.5
unnamed: U3.6 (S2), U5.10
unnamed: U4.14 (GS), U5.12
unnamed: U4.9 (S0), U5.1
unnamed: U4.7 (S1), U5.4
unnamed: U4.6 (S2), U5.9
Rx+: J1.4, U2.R+
Rx-: J1.6, U2.R-
Servo: Conn26.2, U2.23 (A9)
Tx+: J1.1, U2.T+
Tx-: J1.3, U2.T-

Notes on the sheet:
MOCOS
POWER
LASERS
SERVO
Limit Switches
ENCODERS
BUTTONS
BUTTON 16:4 ENCODER
MOUNTS

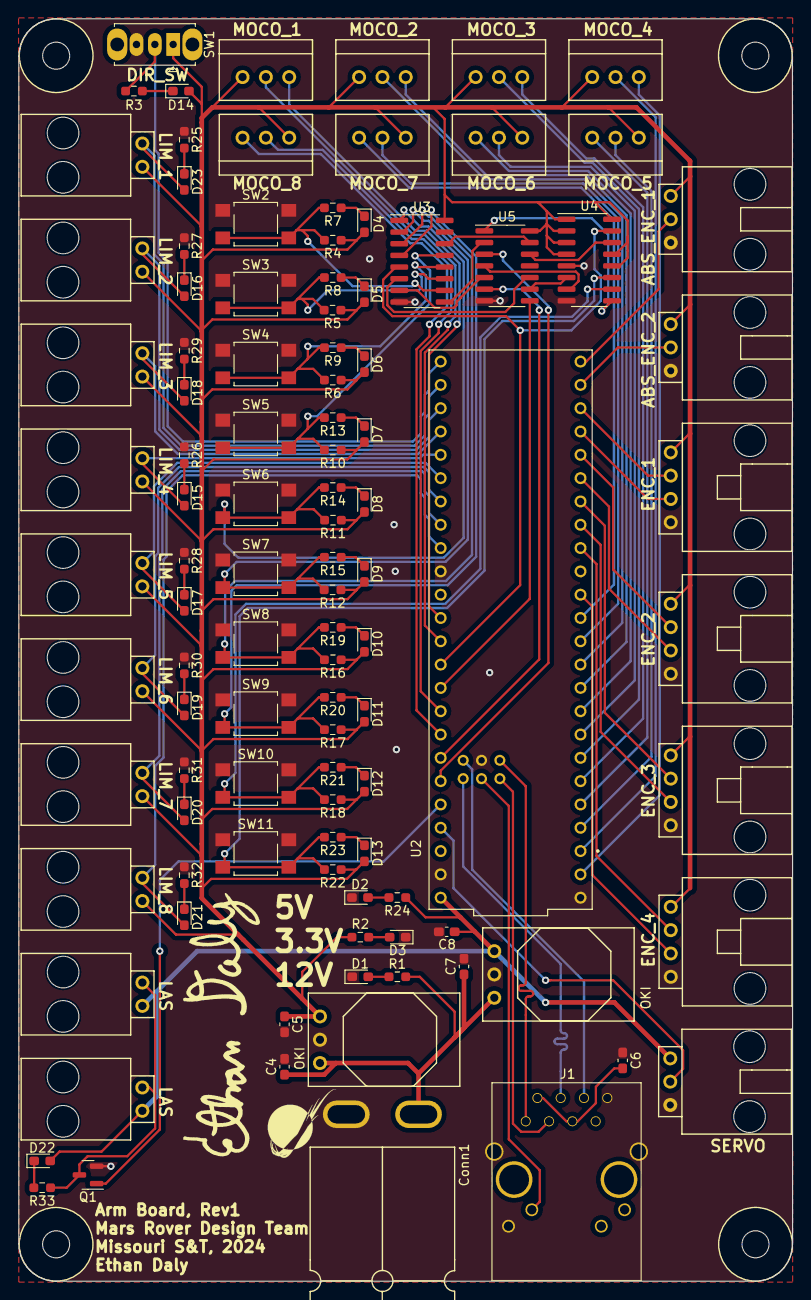
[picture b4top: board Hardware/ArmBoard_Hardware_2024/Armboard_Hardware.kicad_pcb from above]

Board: 2 copper layers, 84.3 x 137.6 mm, 110 parts (0 on the bottom side), 93 nets.
